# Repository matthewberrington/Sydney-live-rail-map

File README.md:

# Sydney-live-train-map

Plan of features:
- [ ] Visualisation of Sydney's L2 & L3 light rail
- [ ] Real time visualisation of tram positions and directions
- [ ] Geographically accurate rail map, extracted from Open Street Map data
- [ ] Geographically accurate silkscreen showing shoreline and points of interest
- [ ] Identify L2 vs L3 trams, and inbound vs outbound from Circulay Quay using different colour encodings of RGB LEDs
- [ ] Legend showing LED colour encoding
- [ ] Seven segment display showing time-to-departure of next service from UNSW Anzac Parade
- [ ] LEDs showing status of connecting rail network (T1, T2, T3, T4, T8, M1, M3, L1)
- [ ] Silscreen tracks of other rail lines (eg, City Circle, Lines south of central)
- [ ] Wi-Fi connectivity
- [ ] Adjustable brightness
- [ ] Train icons at interchanges on silkscreen (T in a circle)
- [ ] L1 line on silkscreen
- [ ] Centenial park 
- [ ] Sydney Harbour bridge

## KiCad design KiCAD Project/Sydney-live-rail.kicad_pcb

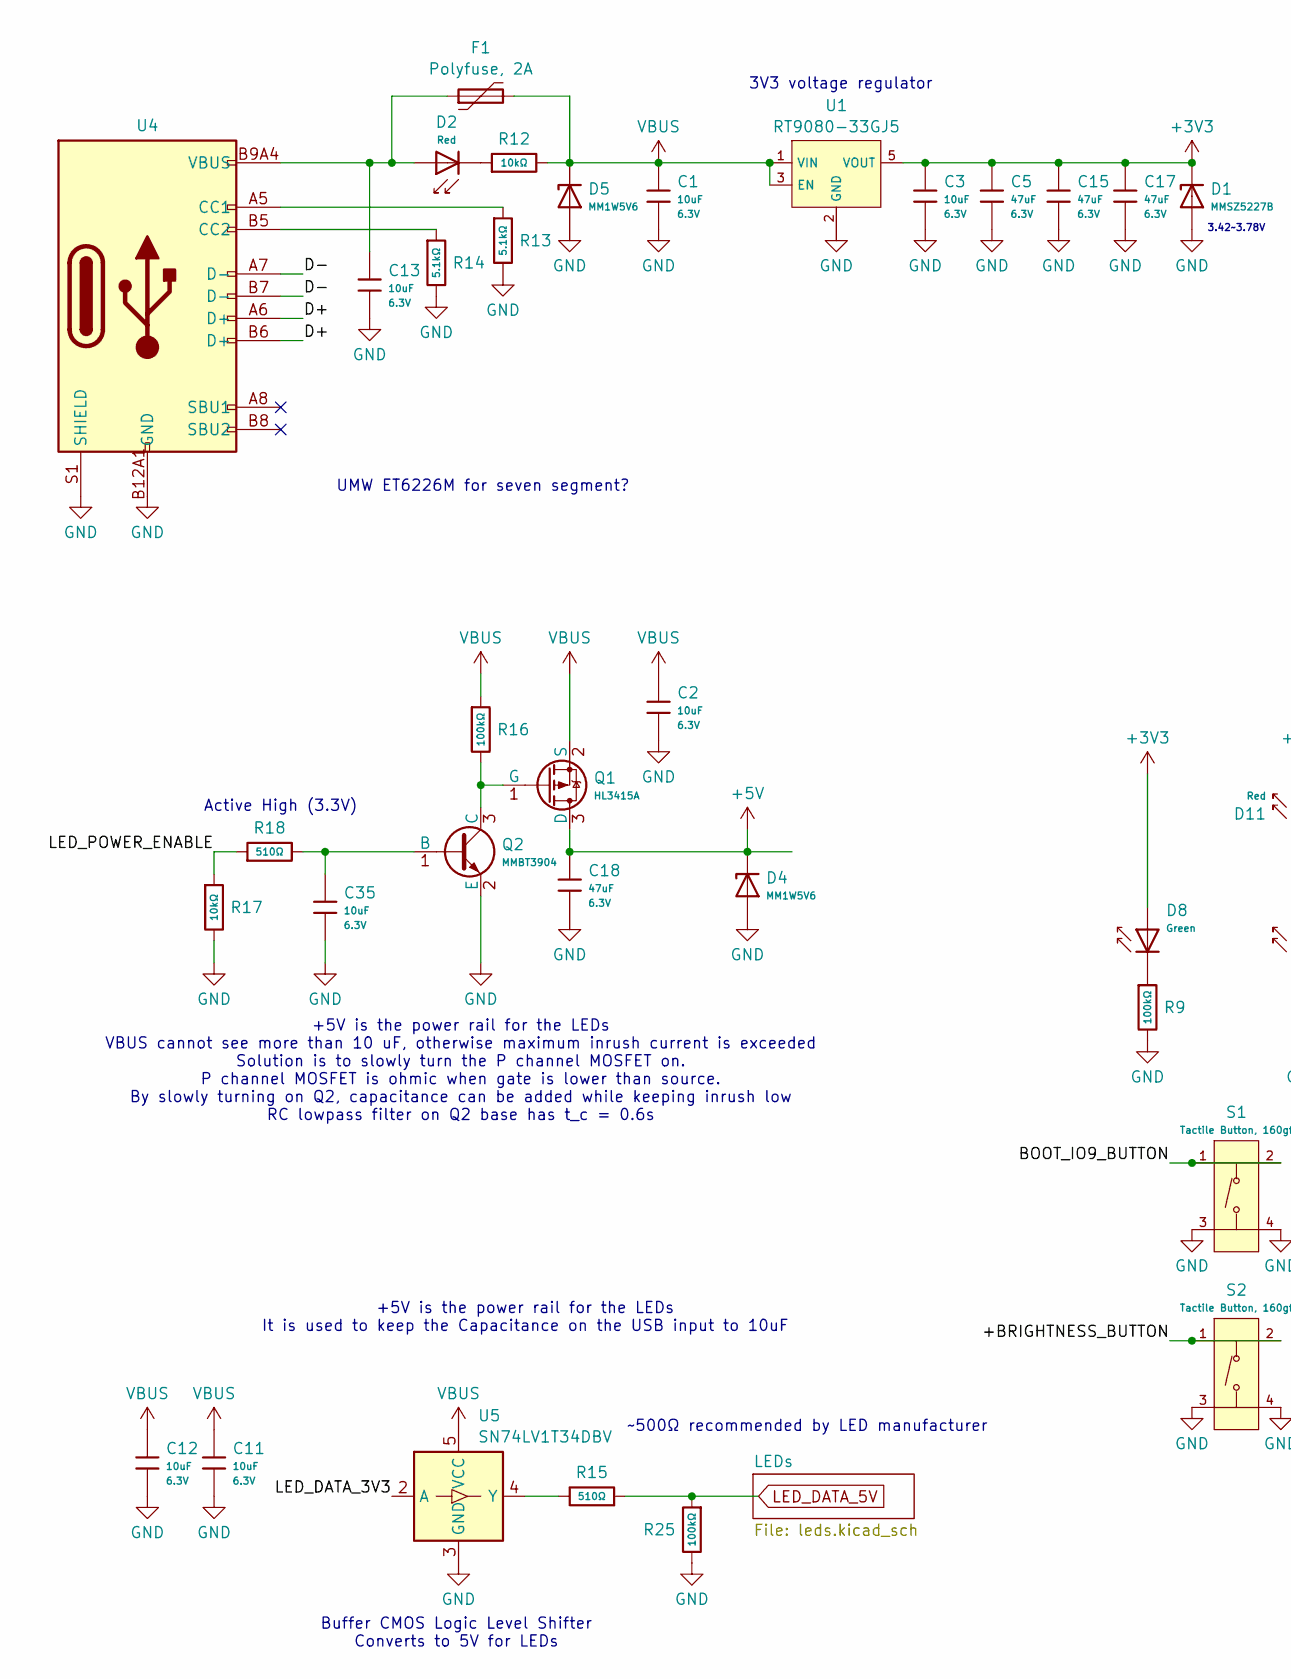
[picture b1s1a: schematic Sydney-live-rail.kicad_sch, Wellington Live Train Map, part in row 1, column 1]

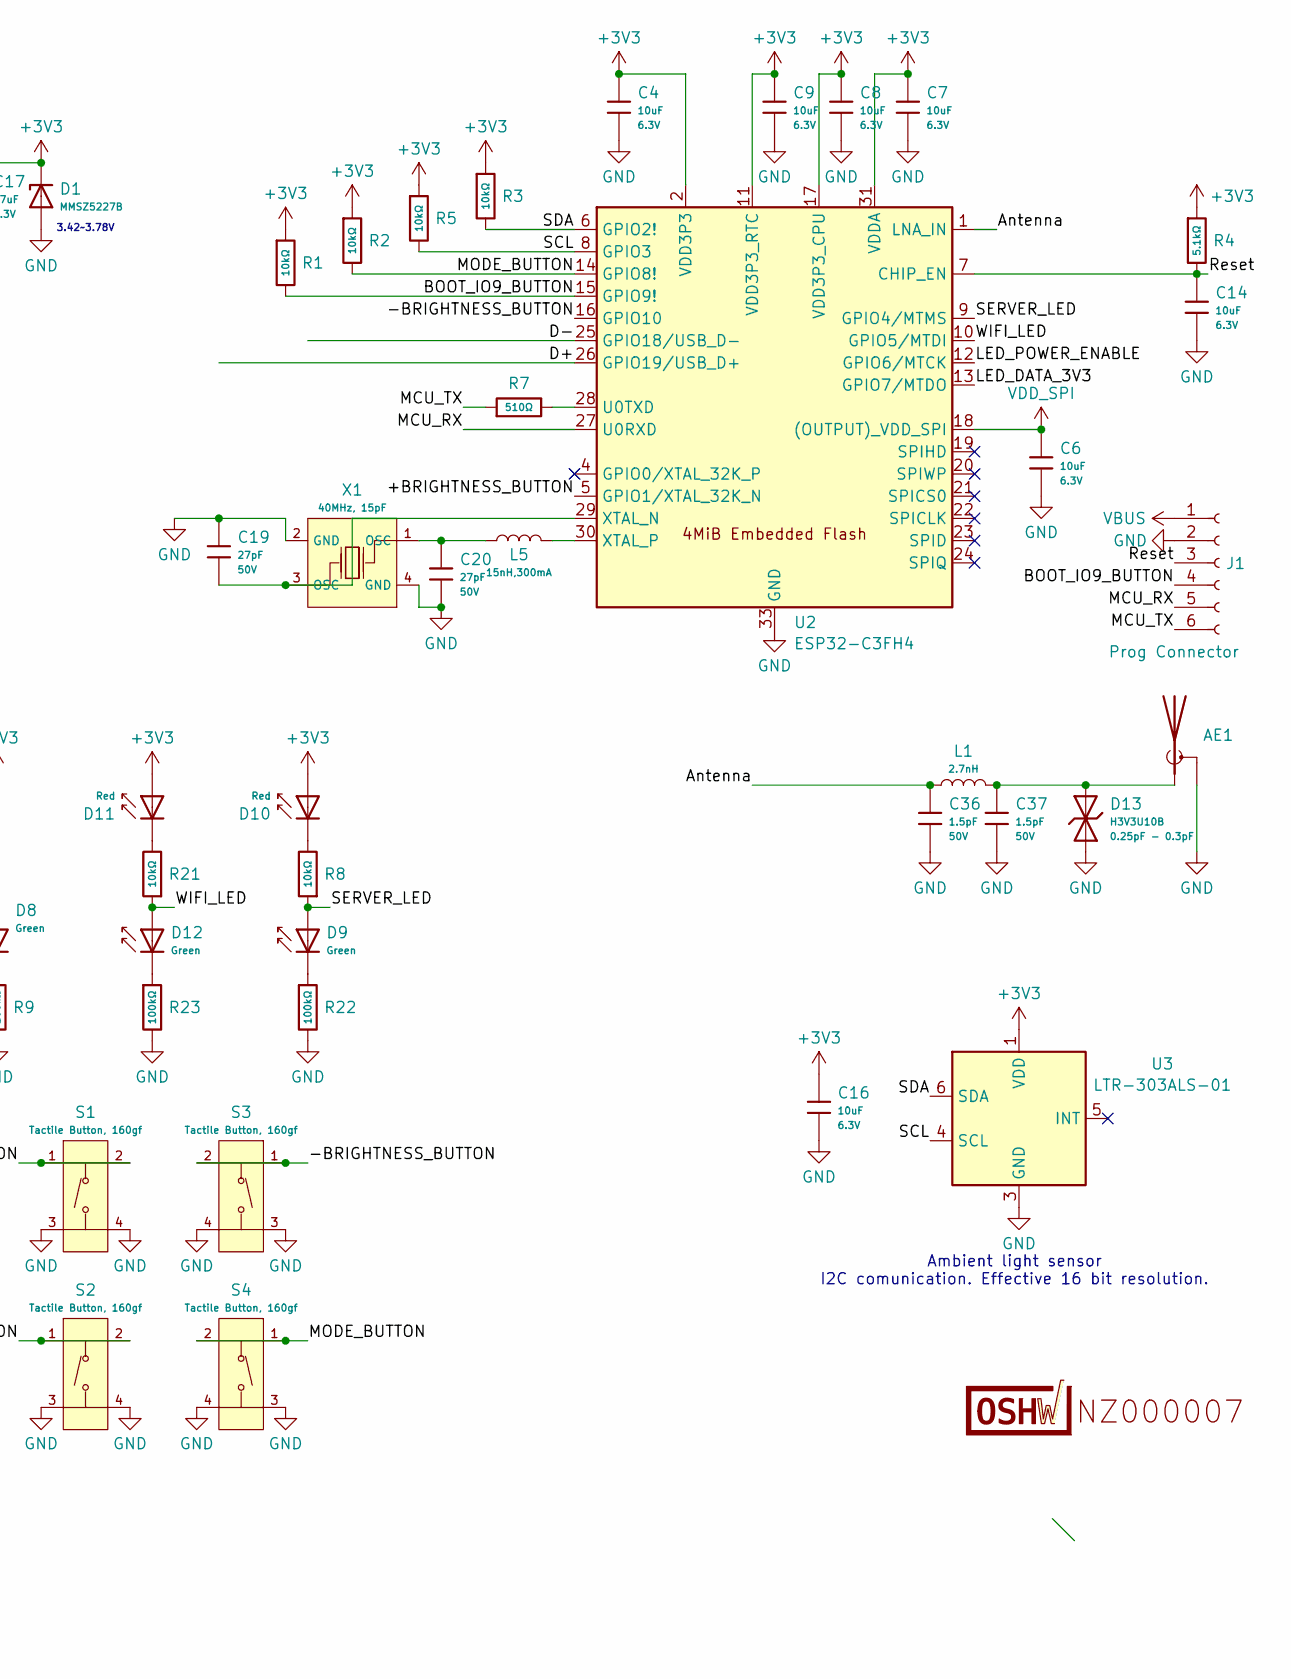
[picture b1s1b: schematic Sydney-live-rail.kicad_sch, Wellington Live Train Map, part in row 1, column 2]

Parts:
AE1: Antenna_Shield; Inverted_F_Antenna_2.4Ghz_1.0mmPCB_TI_CC2430DB.pretty
C1, C2, C3, C4, C6, C7, C8, C9, C11, C12, C13, C14, C16, C35: 10uF; C_0402; Voltage Rated 6.3V; Tolerance ±20%; Part CL05A106MQ5NUNC; LCSC C15525
C5, C15, C17, C18: 47uF; C_0805; Voltage Rated 6.3V; Tolerance ±20%; Part CL21A476MQYNNNE; LCSC C16780
C19, C20: 27pF; C_0402; Voltage Rated 50V; Tolerance ±5%; Part 0402CG270J500NT; LCSC C1557
C36, C37: 1.5pF; C_0402; Voltage Rated 50V; Part 0402CG1R5C500NT; LCSC C1552
D1: MMSZ5227B; D_SOD-123; Part MMSZ5227B; LCSC C22395553
D2, D10, D11: Red; D_0805; Forward Voltage (VF) 1.6V~2.6V; Part NCD0805R1; LCSC C84256
D4, D5: MM1W5V6; D_SOD-123; Part MM1W5V6; LCSC C22435086
D8, D9, D12: Green; D_0805; Part KT-0805G; LCSC C2297
D13: H3V3U10B; D_DFN1006-2L; Part H3V3U10B; LCSC C20615782
F1: Polyfuse, 2A; Fuse_1206_3216Metric; Part SMD1206-200/06N; LCSC C6165195
J1: Prog Connector
L1: 2.7nH; L_0402; Part LQG15HS2N7S02D; LCSC C77108
L5: 15nH,300mA; L_0402; Tolerance ±5%; Part SDCL1005C15NJTDF; LCSC C27143
LOGO2: (no value)
Q1: HL3415A; Q_SOT-23; Part HL3415A; LCSC C28646270
Q2: MMBT3904; Q_SOT-23; Part MMBT3904; LCSC C7420353
R1, R2, R3, R5, R8, R12, R17, R21: 10kΩ; R_0402; Overload Voltage (Max) 50V; Tolerance ±1%; Part 0402WGF1002TCE; LCSC C25744
R4, R13, R14: 5.1kΩ; R_0402; Overload Voltage (Max) 50V; Tolerance ±1%; Part 0402WGF5101TCE; LCSC C25905
R7, R15, R18: 510Ω; R_0402; Overload Voltage (Max) 50V; Tolerance ±1%; Part 0402WGF5100TCE; LCSC C25123
R9, R16, R22, R23, R25: 100kΩ; R_0402; Overload Voltage (Max) 50V; Tolerance ±1%; Part 0402WGF1003TCE; LCSC C25741
S1, S2, S3, S4: Tactile Button, 160gf; SW-SMD_4P-L5.1-W5.1-P3.70-LS6.5-TL-2; Voltage Rating (Dc) 12V; Part TS-1187A-B-A-B; LCSC C318884
U1: RT9080-33GJ5; TSOT-23-5; Part RT9080-33GJ5; LCSC C841192
U2: ESP32-C3FH4; QFN-32-1EP_5x5mm_P0.5mm_EP3.7x3.7mm_ThermalVias; Part ESP32-C3FH4; LCSC C2858491
U3: LTR-303ALS-01; Lite-On_LTR-303ALS-01; Part LTR-303ALS-01; LCSC C364577
U4: Connector, USB-TYPE-C-16P; TYPE-C-SMD_HX-TYPE-C-16PIN; Part USB-TYPE-C-019; LCSC C2927039
U5: SN74LV1T34DBV; SOT-23-5; Part SN74LV1T34DBVR; LCSC C100024
X1: 40MHz, 15pF; OSC-SMD_4P-L3.2-W2.5-BL_SIT8008BI; Part X322540MPB4SI; LCSC C9010

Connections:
+3V3: C3.1, C4.1, C5.1, C7.1, C8.1, C9.1, C15.1, C16.1, C17.1, D1.1, D8.2, D10.2, D11.2, R1.1, R2.1, R3.1, R4.1, R5.1, U1.5 (VOUT), U2.2 (VDD3P3), U2.3 (VDD3P3), U2.11 (VDD3P3_RTC), U2.17 (VDD3P3_CPU), U2.31 (VDDA), U2.32 (VDDA), U3.1 (VDD)
+5V: C18.1, D4.1, Q1.3 (D); also elsewhere on the board
/+BRIGHTNESS_BUTTON: S2.1 (A), S2.2 (B), U2.5 (GPIO1/XTAL_32K_N)
/-BRIGHTNESS_BUTTON: S3.1 (A), S3.2 (B), U2.16 (GPIO10)
/Antenna: C36.1, L1.1, U2.1 (LNA_IN)
/BOOT_IO9_BUTTON: J1.4, R1.2, S1.1 (A), S1.2 (B), U2.15 (GPIO9!)
/D+: U2.26 (GPIO19/USB_D+), U4.A6 (D+), U4.B6 (D+)
/D-: U2.25 (GPIO18/USB_D-), U4.A7 (D-), U4.B7 (D-)
/LED_DATA_3V3: U2.13 (GPIO7/MTDO), U5.2 (A)
/LED_POWER_ENABLE: R17.1, R18.1, U2.12 (GPIO6/MTCK)
/MCU_RX: J1.5, U2.27 (U0RXD)
/MCU_TX: J1.6, R7.1
/MODE_BUTTON: R2.2, S4.1 (A), S4.2 (B), U2.14 (GPIO8!)
/Reset: C14.1, J1.3, R4.2, U2.7 (CHIP_EN)
/SCL: R5.2, U2.8 (GPIO3), U3.4 (SCL)
/SDA: R3.2, U2.6 (GPIO2!), U3.6 (SDA)
/SERVER_LED: D9.2, R8.1, U2.9 (GPIO4/MTMS)
/WIFI_LED: D12.2, R21.1, U2.10 (GPIO5/MTDI)
GND: AE1.2 (Shield), C1.2, C2.2, C3.2, C4.2, C5.2, C6.2, C7.2, C8.2, C9.2, C11.2, C12.2, C13.2, C14.2, C15.2, C16.2, C17.2, C18.2, C19.1, C20.2, C35.2, C36.2, C37.2, D1.2, D4.2, D5.2, D13.1, J1.2, Q2.2 (E), R9.2, R13.2, R14.2, R17.2, R22.2, R23.2, R25.2, S1.3 (C), S1.4 (D), S2.3 (C), S2.4 (D), S3.3 (C), S3.4 (D), S4.3 (C), S4.4 (D), U1.2 (GND), U2.33 (GND), U3.3 (GND), U4.A12B1 (GND), U4.B12A1 (GND), U4.S1 (SHIELD), U5.3 (GND), X1.2 (GND), X1.4 (GND); also elsewhere on the board
LED_DATA_5V: R15.1, R25.1; also elsewhere on the board
unnamed: AE1.1 (A), C37.1, D13.2, L1.2
unnamed: C13.1, D2.2, F1.1, U4.A9B4 (VBUS), U4.B9A4 (VBUS)
unnamed: C20.1, L5.1, X1.1 (OSC)
unnamed: D2.1, R12.1
unnamed: D8.1, R9.1
unnamed: D9.1, R22.1
unnamed: D10.1, R8.2
unnamed: D11.1, R21.2
unnamed: D12.1, R23.1
unnamed: Q1.1 (G), Q2.3 (C), R16.2
unnamed: C35.1, Q2.1 (B), R18.2
unnamed: R7.2, U2.28 (U0TXD)
unnamed: C19.2, U2.29 (XTAL_N), X1.3 (OSC)
unnamed: L5.2, U2.30 (XTAL_P)
unnamed: R13.1, U4.A5 (CC1)
unnamed: R14.1, U4.B5 (CC2)
unnamed: R15.2, U5.4 (Y)
VBUS: C1.1, C2.1, C11.1, C12.1, D5.1, F1.2, J1.1, Q1.2 (S), R12.2, R16.1, U1.1 (VIN), U1.3 (EN), U5.5 (VCC)
VDD_SPI: C6.1, U2.18 ((OUTPUT)_VDD_SPI)

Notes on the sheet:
Active High (3.3V)
+5V is the power rail for the LEDs VBUS cannot see more than 10 uF, otherwise maximum inrush current is exceeded Solution is to slowly turn the P channel MOSFET on. P channel MOSFET is ohmic when gate is lower than source. By slowly turning on Q2, capacitance can be added while keeping inrush low R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
Ambient light sensor I2C comunication. Effective 16 bit resolution.
UMW ET6226M for seven segment?
3V3 voltage regulator
Buffer CMOS Logic Level Shifter Converts to 5V for LEDs
3.42~3.78V
~500Ω recommended by LED manufacturer
+5V is the power rail for the LEDs It is used to keep the Capacitance on the USB input to 10uF

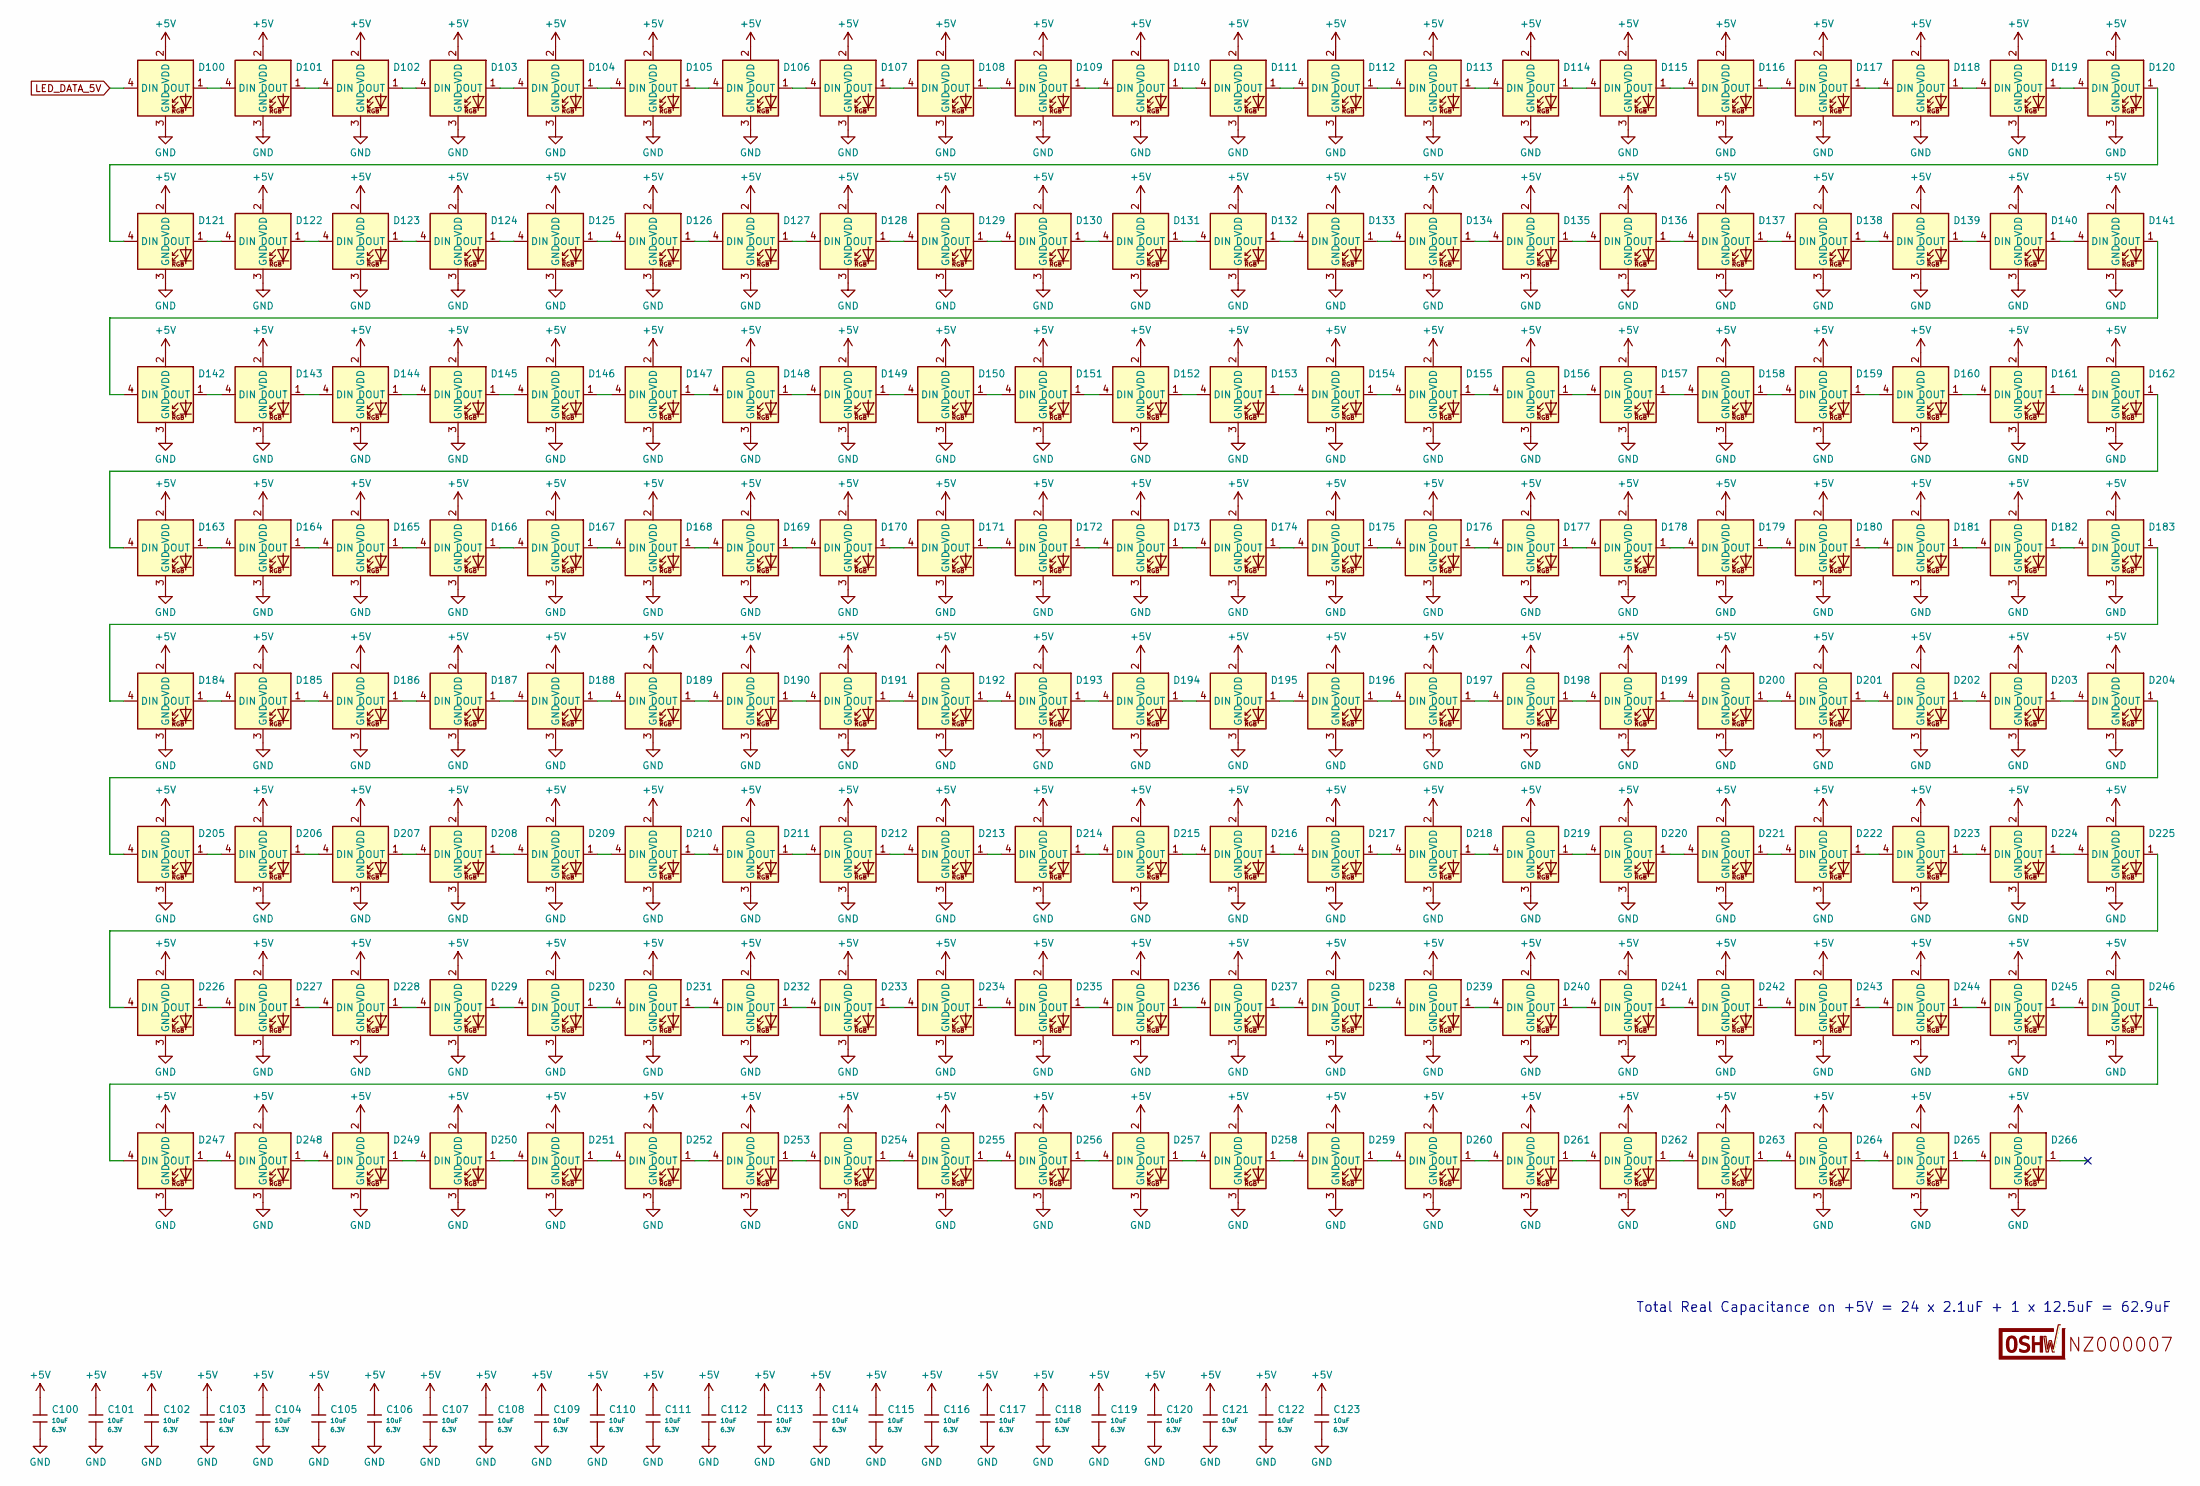
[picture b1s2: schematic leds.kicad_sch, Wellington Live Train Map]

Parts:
C100, C101, C102, C103, C104, C105, C106, C107, C108, C109, C110, C111, C112, C113, C114, C115, C116, C117, C118, C119, C120, C121, C122, C123: 10uF; C_0402; Voltage Rated 6.3V; Tolerance ±20%; Part CL05A106MQ5NUNC; LCSC C15525
D100, D101, D102, D103, D104, D105, D106, D107, D108, D109, D110, D111, D112, D113, D114, D115, D116, D117, D118, D119, D120, D121, D122, D123, D124, D125, D126, D127, D128, D129, D130, D131, D132, D133, D134, D135, D136, D137, D138, D139, D140, D141, D142, D143, D144, D145, D146, D147, D148, D149, D150, D151, D152, D153, D154, D155, D156, D157, D158, D159, D160, D161, D162, D163, D164, D165, D166, D167, D168, D169, D170, D171, D172, D173, D174, D175, D176, D177, D178, D179, D180, D181, D182, D183, D184, D185, D186, D187, D188, D189, D190, D191, D192, D193, D194, D195, D196, D197, D198, D199, D200, D201, D202, D203, D204, D205, D206, D207, D208, D209, D210, D211, D212, D213, D214, D215, D216, D217, D218, D219, D220, D221, D222, D223, D224, D225, D226, D227, D228, D229, D230, D231, D232, D233, D234, D235, D236, D237, D238, D239, D240, D241, D242, D243, D244, D245, D246, D247, D248, D249, D250, D251, D252, D253, D254, D255, D256, D257, D258, D259, D260, D261, D262, D263, D264, D265, D266: XL-1615RGBC-WS2812B-S; LED-SMD_4P-L1.6-W1.5_XL-1615RGBC-WS2812B; Part XL-1615RGBC-WS2812B-S; LCSC C41413180
LOGO1: (no value)

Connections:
+5V: C100.1, C101.1, C102.1, C103.1, C104.1, C105.1, C106.1, C107.1, C108.1, C109.1, C110.1, C111.1, C112.1, C113.1, C114.1, C115.1, C116.1, C117.1, C118.1, C119.1, C120.1, C121.1, C122.1, C123.1, D100.2 (VDD), D101.2 (VDD), D102.2 (VDD), D103.2 (VDD), D104.2 (VDD), D105.2 (VDD), D106.2 (VDD), D107.2 (VDD), D108.2 (VDD), D109.2 (VDD), D110.2 (VDD), D111.2 (VDD), D112.2 (VDD), D113.2 (VDD), D114.2 (VDD), D115.2 (VDD), D116.2 (VDD), D117.2 (VDD), D118.2 (VDD), D119.2 (VDD), D120.2 (VDD), D121.2 (VDD), D122.2 (VDD), D123.2 (VDD), D124.2 (VDD), D125.2 (VDD), D126.2 (VDD), D127.2 (VDD), D128.2 (VDD), D129.2 (VDD), D130.2 (VDD), D131.2 (VDD), D132.2 (VDD), D133.2 (VDD), D134.2 (VDD), D135.2 (VDD), D136.2 (VDD), D137.2 (VDD), D138.2 (VDD), D139.2 (VDD), D140.2 (VDD), D141.2 (VDD), D142.2 (VDD), D143.2 (VDD), D144.2 (VDD), D145.2 (VDD), D146.2 (VDD), D147.2 (VDD), D148.2 (VDD), D149.2 (VDD), D150.2 (VDD), D151.2 (VDD), D152.2 (VDD), D153.2 (VDD), D154.2 (VDD), D155.2 (VDD), D156.2 (VDD), D157.2 (VDD), D158.2 (VDD), D159.2 (VDD), D160.2 (VDD), D161.2 (VDD), D162.2 (VDD), D163.2 (VDD), D164.2 (VDD), D165.2 (VDD), D166.2 (VDD), D167.2 (VDD), D168.2 (VDD), D169.2 (VDD), D170.2 (VDD), D171.2 (VDD), D172.2 (VDD), D173.2 (VDD), D174.2 (VDD), D175.2 (VDD), D176.2 (VDD), D177.2 (VDD), D178.2 (VDD), D179.2 (VDD), D180.2 (VDD), D181.2 (VDD), D182.2 (VDD), D183.2 (VDD), D184.2 (VDD), D185.2 (VDD), D186.2 (VDD), D187.2 (VDD), D188.2 (VDD), D189.2 (VDD), D190.2 (VDD), D191.2 (VDD), D192.2 (VDD), D193.2 (VDD), D194.2 (VDD), D195.2 (VDD), D196.2 (VDD), D197.2 (VDD), D198.2 (VDD), D199.2 (VDD), D200.2 (VDD), D201.2 (VDD), D202.2 (VDD), D203.2 (VDD), D204.2 (VDD), D205.2 (VDD), D206.2 (VDD), D207.2 (VDD), D208.2 (VDD), D209.2 (VDD), D210.2 (VDD), D211.2 (VDD), D212.2 (VDD), D213.2 (VDD), D214.2 (VDD), D215.2 (VDD), D216.2 (VDD), D217.2 (VDD), D218.2 (VDD), D219.2 (VDD), D220.2 (VDD), D221.2 (VDD), D222.2 (VDD), D223.2 (VDD), D224.2 (VDD), D225.2 (VDD), D226.2 (VDD), D227.2 (VDD), D228.2 (VDD), D229.2 (VDD), D230.2 (VDD), D231.2 (VDD), D232.2 (VDD), D233.2 (VDD), D234.2 (VDD), D235.2 (VDD), D236.2 (VDD), D237.2 (VDD), D238.2 (VDD), D239.2 (VDD), D240.2 (VDD), D241.2 (VDD), D242.2 (VDD), D243.2 (VDD), D244.2 (VDD), D245.2 (VDD), D246.2 (VDD), D247.2 (VDD), D248.2 (VDD), D249.2 (VDD), D250.2 (VDD), D251.2 (VDD), D252.2 (VDD), D253.2 (VDD), D254.2 (VDD), D255.2 (VDD), D256.2 (VDD), D257.2 (VDD), D258.2 (VDD), D259.2 (VDD), D260.2 (VDD), D261.2 (VDD), D262.2 (VDD), D263.2 (VDD), D264.2 (VDD), D265.2 (VDD), D266.2 (VDD); also elsewhere on the board
GND: C100.2, C101.2, C102.2, C103.2, C104.2, C105.2, C106.2, C107.2, C108.2, C109.2, C110.2, C111.2, C112.2, C113.2, C114.2, C115.2, C116.2, C117.2, C118.2, C119.2, C120.2, C121.2, C122.2, C123.2, D100.3 (GND), D101.3 (GND), D102.3 (GND), D103.3 (GND), D104.3 (GND), D105.3 (GND), D106.3 (GND), D107.3 (GND), D108.3 (GND), D109.3 (GND), D110.3 (GND), D111.3 (GND), D112.3 (GND), D113.3 (GND), D114.3 (GND), D115.3 (GND), D116.3 (GND), D117.3 (GND), D118.3 (GND), D119.3 (GND), D120.3 (GND), D121.3 (GND), D122.3 (GND), D123.3 (GND), D124.3 (GND), D125.3 (GND), D126.3 (GND), D127.3 (GND), D128.3 (GND), D129.3 (GND), D130.3 (GND), D131.3 (GND), D132.3 (GND), D133.3 (GND), D134.3 (GND), D135.3 (GND), D136.3 (GND), D137.3 (GND), D138.3 (GND), D139.3 (GND), D140.3 (GND), D141.3 (GND), D142.3 (GND), D143.3 (GND), D144.3 (GND), D145.3 (GND), D146.3 (GND), D147.3 (GND), D148.3 (GND), D149.3 (GND), D150.3 (GND), D151.3 (GND), D152.3 (GND), D153.3 (GND), D154.3 (GND), D155.3 (GND), D156.3 (GND), D157.3 (GND), D158.3 (GND), D159.3 (GND), D160.3 (GND), D161.3 (GND), D162.3 (GND), D163.3 (GND), D164.3 (GND), D165.3 (GND), D166.3 (GND), D167.3 (GND), D168.3 (GND), D169.3 (GND), D170.3 (GND), D171.3 (GND), D172.3 (GND), D173.3 (GND), D174.3 (GND), D175.3 (GND), D176.3 (GND), D177.3 (GND), D178.3 (GND), D179.3 (GND), D180.3 (GND), D181.3 (GND), D182.3 (GND), D183.3 (GND), D184.3 (GND), D185.3 (GND), D186.3 (GND), D187.3 (GND), D188.3 (GND), D189.3 (GND), D190.3 (GND), D191.3 (GND), D192.3 (GND), D193.3 (GND), D194.3 (GND), D195.3 (GND), D196.3 (GND), D197.3 (GND), D198.3 (GND), D199.3 (GND), D200.3 (GND), D201.3 (GND), D202.3 (GND), D203.3 (GND), D204.3 (GND), D205.3 (GND), D206.3 (GND), D207.3 (GND), D208.3 (GND), D209.3 (GND), D210.3 (GND), D211.3 (GND), D212.3 (GND), D213.3 (GND), D214.3 (GND), D215.3 (GND), D216.3 (GND), D217.3 (GND), D218.3 (GND), D219.3 (GND), D220.3 (GND), D221.3 (GND), D222.3 (GND), D223.3 (GND), D224.3 (GND), D225.3 (GND), D226.3 (GND), D227.3 (GND), D228.3 (GND), D229.3 (GND), D230.3 (GND), D231.3 (GND), D232.3 (GND), D233.3 (GND), D234.3 (GND), D235.3 (GND), D236.3 (GND), D237.3 (GND), D238.3 (GND), D239.3 (GND), D240.3 (GND), D241.3 (GND), D242.3 (GND), D243.3 (GND), D244.3 (GND), D245.3 (GND), D246.3 (GND), D247.3 (GND), D248.3 (GND), D249.3 (GND), D250.3 (GND), D251.3 (GND), D252.3 (GND), D253.3 (GND), D254.3 (GND), D255.3 (GND), D256.3 (GND), D257.3 (GND), D258.3 (GND), D259.3 (GND), D260.3 (GND), D261.3 (GND), D262.3 (GND), D263.3 (GND), D264.3 (GND), D265.3 (GND), D266.3 (GND); also elsewhere on the board
LED_DATA_5V: D100.4 (DIN); also elsewhere on the board
unnamed: D100.1 (DOUT), D101.4 (DIN)
unnamed: D101.1 (DOUT), D102.4 (DIN)
unnamed: D102.1 (DOUT), D103.4 (DIN)
unnamed: D103.1 (DOUT), D104.4 (DIN)
unnamed: D104.1 (DOUT), D105.4 (DIN)
unnamed: D105.1 (DOUT), D106.4 (DIN)
unnamed: D106.1 (DOUT), D107.4 (DIN)
unnamed: D107.1 (DOUT), D108.4 (DIN)
unnamed: D108.1 (DOUT), D109.4 (DIN)
unnamed: D109.1 (DOUT), D110.4 (DIN)
unnamed: D110.1 (DOUT), D111.4 (DIN)
unnamed: D111.1 (DOUT), D112.4 (DIN)
unnamed: D112.1 (DOUT), D113.4 (DIN)
unnamed: D113.1 (DOUT), D114.4 (DIN)
unnamed: D114.1 (DOUT), D115.4 (DIN)
unnamed: D115.1 (DOUT), D116.4 (DIN)
unnamed: D116.1 (DOUT), D117.4 (DIN)
unnamed: D117.1 (DOUT), D118.4 (DIN)
unnamed: D118.1 (DOUT), D119.4 (DIN)
unnamed: D119.1 (DOUT), D120.4 (DIN)
unnamed: D120.1 (DOUT), D121.4 (DIN)
unnamed: D121.1 (DOUT), D122.4 (DIN)
unnamed: D122.1 (DOUT), D123.4 (DIN)
unnamed: D123.1 (DOUT), D124.4 (DIN)
unnamed: D124.1 (DOUT), D125.4 (DIN)
unnamed: D125.1 (DOUT), D126.4 (DIN)
unnamed: D126.1 (DOUT), D127.4 (DIN)
unnamed: D127.1 (DOUT), D128.4 (DIN)
unnamed: D128.1 (DOUT), D129.4 (DIN)
unnamed: D129.1 (DOUT), D130.4 (DIN)
unnamed: D130.1 (DOUT), D131.4 (DIN)
unnamed: D131.1 (DOUT), D132.4 (DIN)
unnamed: D132.1 (DOUT), D133.4 (DIN)
unnamed: D133.1 (DOUT), D134.4 (DIN)
unnamed: D134.1 (DOUT), D135.4 (DIN)
unnamed: D135.1 (DOUT), D136.4 (DIN)
unnamed: D136.1 (DOUT), D137.4 (DIN)
unnamed: D137.1 (DOUT), D138.4 (DIN)
unnamed: D138.1 (DOUT), D139.4 (DIN)
unnamed: D139.1 (DOUT), D140.4 (DIN)
unnamed: D140.1 (DOUT), D141.4 (DIN)
unnamed: D141.1 (DOUT), D142.4 (DIN)
unnamed: D142.1 (DOUT), D143.4 (DIN)
unnamed: D143.1 (DOUT), D144.4 (DIN)
unnamed: D144.1 (DOUT), D145.4 (DIN)
unnamed: D145.1 (DOUT), D146.4 (DIN)
unnamed: D146.1 (DOUT), D147.4 (DIN)
unnamed: D147.1 (DOUT), D148.4 (DIN)
unnamed: D148.1 (DOUT), D149.4 (DIN)
unnamed: D149.1 (DOUT), D150.4 (DIN)
unnamed: D150.1 (DOUT), D151.4 (DIN)
unnamed: D151.1 (DOUT), D152.4 (DIN)
unnamed: D152.1 (DOUT), D153.4 (DIN)
unnamed: D153.1 (DOUT), D154.4 (DIN)
unnamed: D154.1 (DOUT), D155.4 (DIN)
unnamed: D155.1 (DOUT), D156.4 (DIN)
unnamed: D156.1 (DOUT), D157.4 (DIN)
unnamed: D157.1 (DOUT), D158.4 (DIN)
unnamed: D158.1 (DOUT), D159.4 (DIN)
unnamed: D159.1 (DOUT), D160.4 (DIN)
unnamed: D160.1 (DOUT), D161.4 (DIN)
unnamed: D161.1 (DOUT), D162.4 (DIN)
unnamed: D162.1 (DOUT), D163.4 (DIN)
unnamed: D163.1 (DOUT), D164.4 (DIN)
unnamed: D164.1 (DOUT), D165.4 (DIN)
unnamed: D165.1 (DOUT), D166.4 (DIN)
unnamed: D166.1 (DOUT), D167.4 (DIN)
unnamed: D167.1 (DOUT), D168.4 (DIN)
unnamed: D168.1 (DOUT), D169.4 (DIN)
unnamed: D169.1 (DOUT), D170.4 (DIN)
unnamed: D170.1 (DOUT), D171.4 (DIN)
unnamed: D171.1 (DOUT), D172.4 (DIN)
unnamed: D172.1 (DOUT), D173.4 (DIN)
unnamed: D173.1 (DOUT), D174.4 (DIN)
unnamed: D174.1 (DOUT), D175.4 (DIN)
unnamed: D175.1 (DOUT), D176.4 (DIN)
unnamed: D176.1 (DOUT), D177.4 (DIN)
unnamed: D177.1 (DOUT), D178.4 (DIN)
unnamed: D178.1 (DOUT), D179.4 (DIN)
unnamed: D179.1 (DOUT), D180.4 (DIN)
unnamed: D180.1 (DOUT), D181.4 (DIN)
unnamed: D181.1 (DOUT), D182.4 (DIN)
unnamed: D182.1 (DOUT), D183.4 (DIN)
unnamed: D183.1 (DOUT), D184.4 (DIN)
unnamed: D184.1 (DOUT), D185.4 (DIN)
unnamed: D185.1 (DOUT), D186.4 (DIN)
unnamed: D186.1 (DOUT), D187.4 (DIN)
unnamed: D187.1 (DOUT), D188.4 (DIN)
unnamed: D188.1 (DOUT), D189.4 (DIN)
unnamed: D189.1 (DOUT), D190.4 (DIN)
unnamed: D190.1 (DOUT), D191.4 (DIN)
unnamed: D191.1 (DOUT), D192.4 (DIN)
unnamed: D192.1 (DOUT), D193.4 (DIN)
unnamed: D193.1 (DOUT), D194.4 (DIN)
unnamed: D194.1 (DOUT), D195.4 (DIN)
unnamed: D195.1 (DOUT), D196.4 (DIN)
unnamed: D196.1 (DOUT), D197.4 (DIN)
unnamed: D197.1 (DOUT), D198.4 (DIN)
unnamed: D198.1 (DOUT), D199.4 (DIN)
unnamed: D199.1 (DOUT), D200.4 (DIN)
unnamed: D200.1 (DOUT), D201.4 (DIN)
unnamed: D201.1 (DOUT), D202.4 (DIN)
unnamed: D202.1 (DOUT), D203.4 (DIN)
unnamed: D203.1 (DOUT), D204.4 (DIN)
unnamed: D204.1 (DOUT), D205.4 (DIN)
unnamed: D205.1 (DOUT), D206.4 (DIN)
unnamed: D206.1 (DOUT), D207.4 (DIN)
unnamed: D207.1 (DOUT), D208.4 (DIN)
unnamed: D208.1 (DOUT), D209.4 (DIN)
unnamed: D209.1 (DOUT), D210.4 (DIN)
unnamed: D210.1 (DOUT), D211.4 (DIN)
unnamed: D211.1 (DOUT), D212.4 (DIN)
unnamed: D212.1 (DOUT), D213.4 (DIN)
unnamed: D213.1 (DOUT), D214.4 (DIN)
unnamed: D214.1 (DOUT), D215.4 (DIN)
unnamed: D215.1 (DOUT), D216.4 (DIN)
unnamed: D216.1 (DOUT), D217.4 (DIN)
unnamed: D217.1 (DOUT), D218.4 (DIN)
unnamed: D218.1 (DOUT), D219.4 (DIN)
unnamed: D219.1 (DOUT), D220.4 (DIN)
unnamed: D220.1 (DOUT), D221.4 (DIN)
unnamed: D221.1 (DOUT), D222.4 (DIN)
unnamed: D222.1 (DOUT), D223.4 (DIN)
unnamed: D223.1 (DOUT), D224.4 (DIN)
unnamed: D224.1 (DOUT), D225.4 (DIN)
unnamed: D225.1 (DOUT), D226.4 (DIN)
unnamed: D226.1 (DOUT), D227.4 (DIN)
unnamed: D227.1 (DOUT), D228.4 (DIN)
unnamed: D228.1 (DOUT), D229.4 (DIN)
unnamed: D229.1 (DOUT), D230.4 (DIN)
unnamed: D230.1 (DOUT), D231.4 (DIN)
unnamed: D231.1 (DOUT), D232.4 (DIN)
unnamed: D232.1 (DOUT), D233.4 (DIN)
unnamed: D233.1 (DOUT), D234.4 (DIN)
unnamed: D234.1 (DOUT), D235.4 (DIN)
unnamed: D235.1 (DOUT), D236.4 (DIN)
unnamed: D236.1 (DOUT), D237.4 (DIN)
unnamed: D237.1 (DOUT), D238.4 (DIN)
unnamed: D238.1 (DOUT), D239.4 (DIN)
unnamed: D239.1 (DOUT), D240.4 (DIN)
unnamed: D240.1 (DOUT), D241.4 (DIN)
unnamed: D241.1 (DOUT), D242.4 (DIN)
unnamed: D242.1 (DOUT), D243.4 (DIN)
unnamed: D243.1 (DOUT), D244.4 (DIN)
unnamed: D244.1 (DOUT), D245.4 (DIN)
unnamed: D245.1 (DOUT), D246.4 (DIN)
unnamed: D246.1 (DOUT), D247.4 (DIN)
unnamed: D247.1 (DOUT), D248.4 (DIN)
unnamed: D248.1 (DOUT), D249.4 (DIN)
unnamed: D249.1 (DOUT), D250.4 (DIN)
unnamed: D250.1 (DOUT), D251.4 (DIN)
unnamed: D251.1 (DOUT), D252.4 (DIN)
unnamed: D252.1 (DOUT), D253.4 (DIN)
unnamed: D253.1 (DOUT), D254.4 (DIN)
unnamed: D254.1 (DOUT), D255.4 (DIN)
unnamed: D255.1 (DOUT), D256.4 (DIN)
unnamed: D256.1 (DOUT), D257.4 (DIN)
unnamed: D257.1 (DOUT), D258.4 (DIN)
unnamed: D258.1 (DOUT), D259.4 (DIN)
unnamed: D259.1 (DOUT), D260.4 (DIN)
unnamed: D260.1 (DOUT), D261.4 (DIN)
unnamed: D261.1 (DOUT), D262.4 (DIN)
unnamed: D262.1 (DOUT), D263.4 (DIN)
unnamed: D263.1 (DOUT), D264.4 (DIN)
unnamed: D264.1 (DOUT), D265.4 (DIN)
unnamed: D265.1 (DOUT), D266.4 (DIN)

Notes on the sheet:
Total Real Capacitance on +5V = 24 x 2.1uF + 1 x 12.5uF = 62.9uF

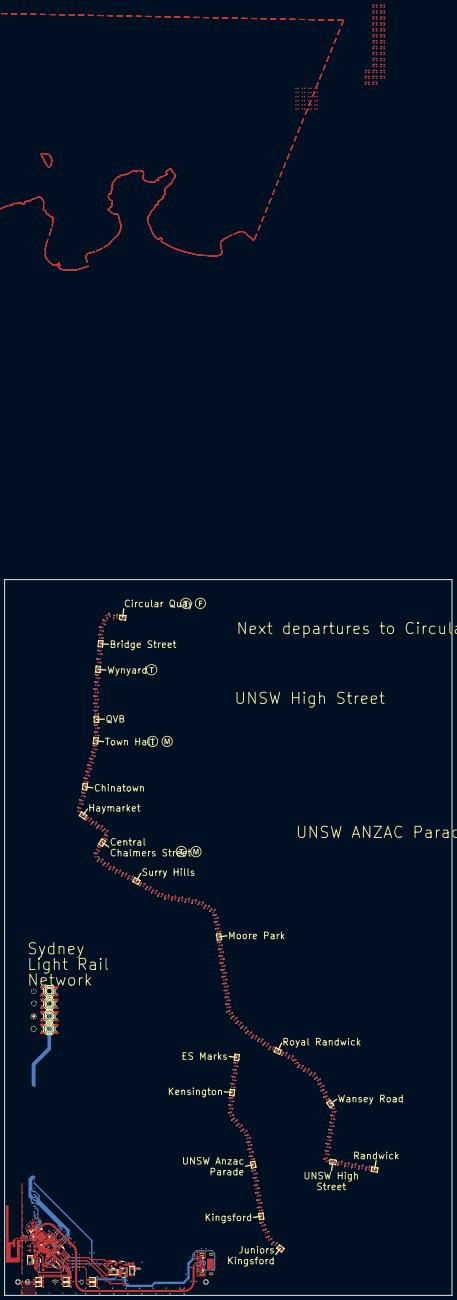
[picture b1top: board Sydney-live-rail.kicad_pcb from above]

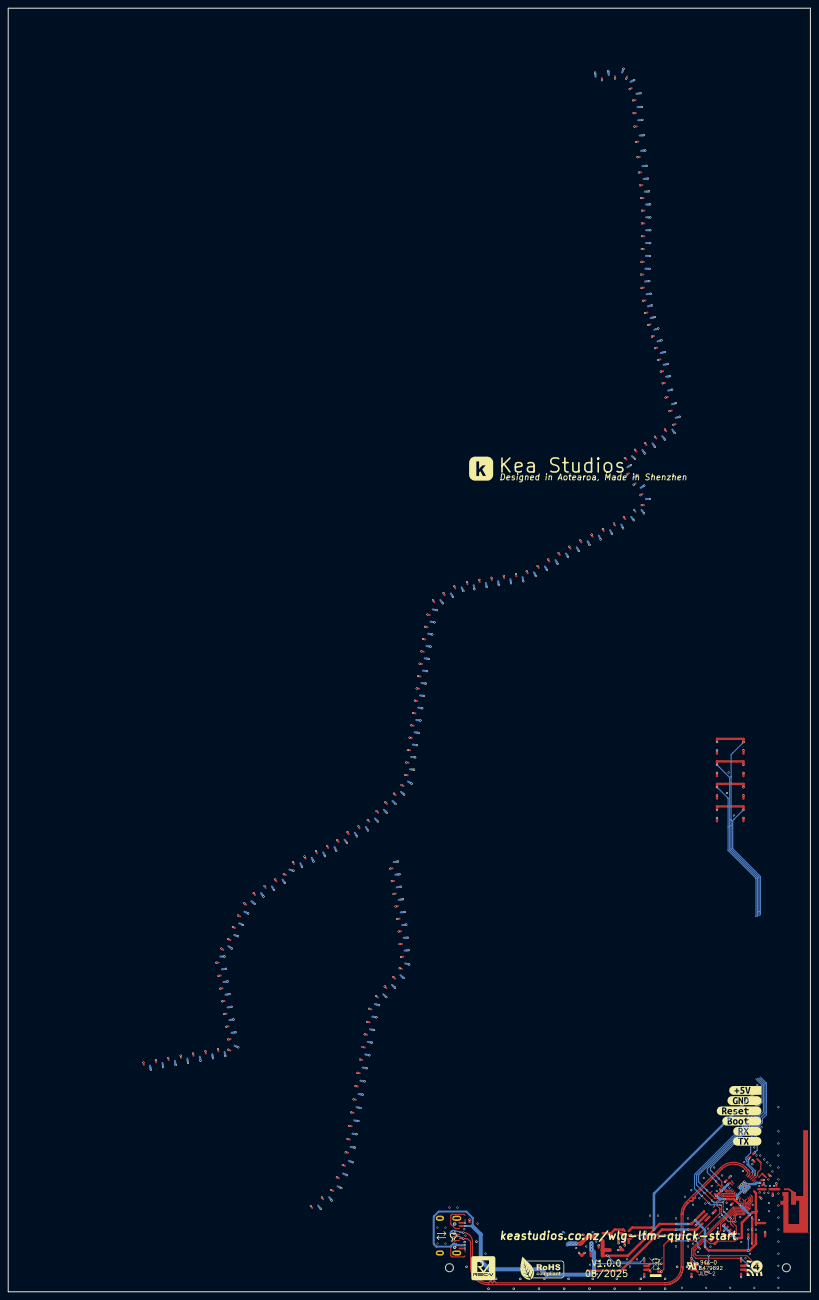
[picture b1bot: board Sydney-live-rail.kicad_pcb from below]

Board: 2 copper layers, 200.0 x 320.0 mm, 265 parts (6 on the bottom side), 205 nets.

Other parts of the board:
kibuzzard-68A93B9D: G***; kibuzzard-68A93B9D
kibuzzard-68A93BAB: G***; kibuzzard-68A93BAB
kibuzzard-68A93BBD: G***; kibuzzard-68A93BBD
kibuzzard-68A93BCF: G***; kibuzzard-68A93BCF
kibuzzard-68A93BEA: G***; kibuzzard-68A93BEA
kibuzzard-68A93BF1: G***; kibuzzard-68A93BF1

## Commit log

2025-10-21 Adding license and readme
2025-10-21 Separate lightrail and coastline digesters
2025-10-22 Renaming files
2025-10-22 Move gneeric geospatial functions to utils_geospatial.py
2025-10-22 Show all track features in digest to compare LEDs to real map easily
2025-10-22 Adding planned features
2025-10-24 Added annotations to schematic
2025-10-27 Brainstorming more features to do
2026-03-23 Make coasline pckl only include coastline within the PCB area
2026-03-24 Made harbour a copper pour
2026-03-24 Added digest track
2026-03-25 Adding Station class
2026-03-28 Got digest_track.py working to calculate position of LEDs
2026-03-29 Got digestion working with class structures
2026-03-30 Got LED placement working with correct orientation
2026-03-31 Got VSS automatically routed for LEDs
2026-03-31 Started using Codex and added labels to stations
2026-03-31 Made station labels more legible
2026-03-31 Shifted PCB to be centred on page
2026-03-31 Added control electronics from Wellington project
2026-04-01 Added in train digester
2026-04-01 Added Metro icon
2026-04-01 Added train lines to solder mask
2026-04-01 Locked components not generate by python
2026-04-01 Fixed coastline so it's aligned with pcb
2026-04-01 Only plot train tracks within pcb boundary
2026-04-01 Added GND pour
2026-04-03 Fixed errors and warning on PCB
2026-04-03 Added ground planes aroung PCB
2026-04-03 Fixed font again
2026-04-03 Set sydney transport symbols to 5mm tall
2026-04-03 Roboto Slab font

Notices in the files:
KiCAD Project/Sydney-live-rail.kicad_sch:
©Chris Dirks
GPL-3.0-or-later License
